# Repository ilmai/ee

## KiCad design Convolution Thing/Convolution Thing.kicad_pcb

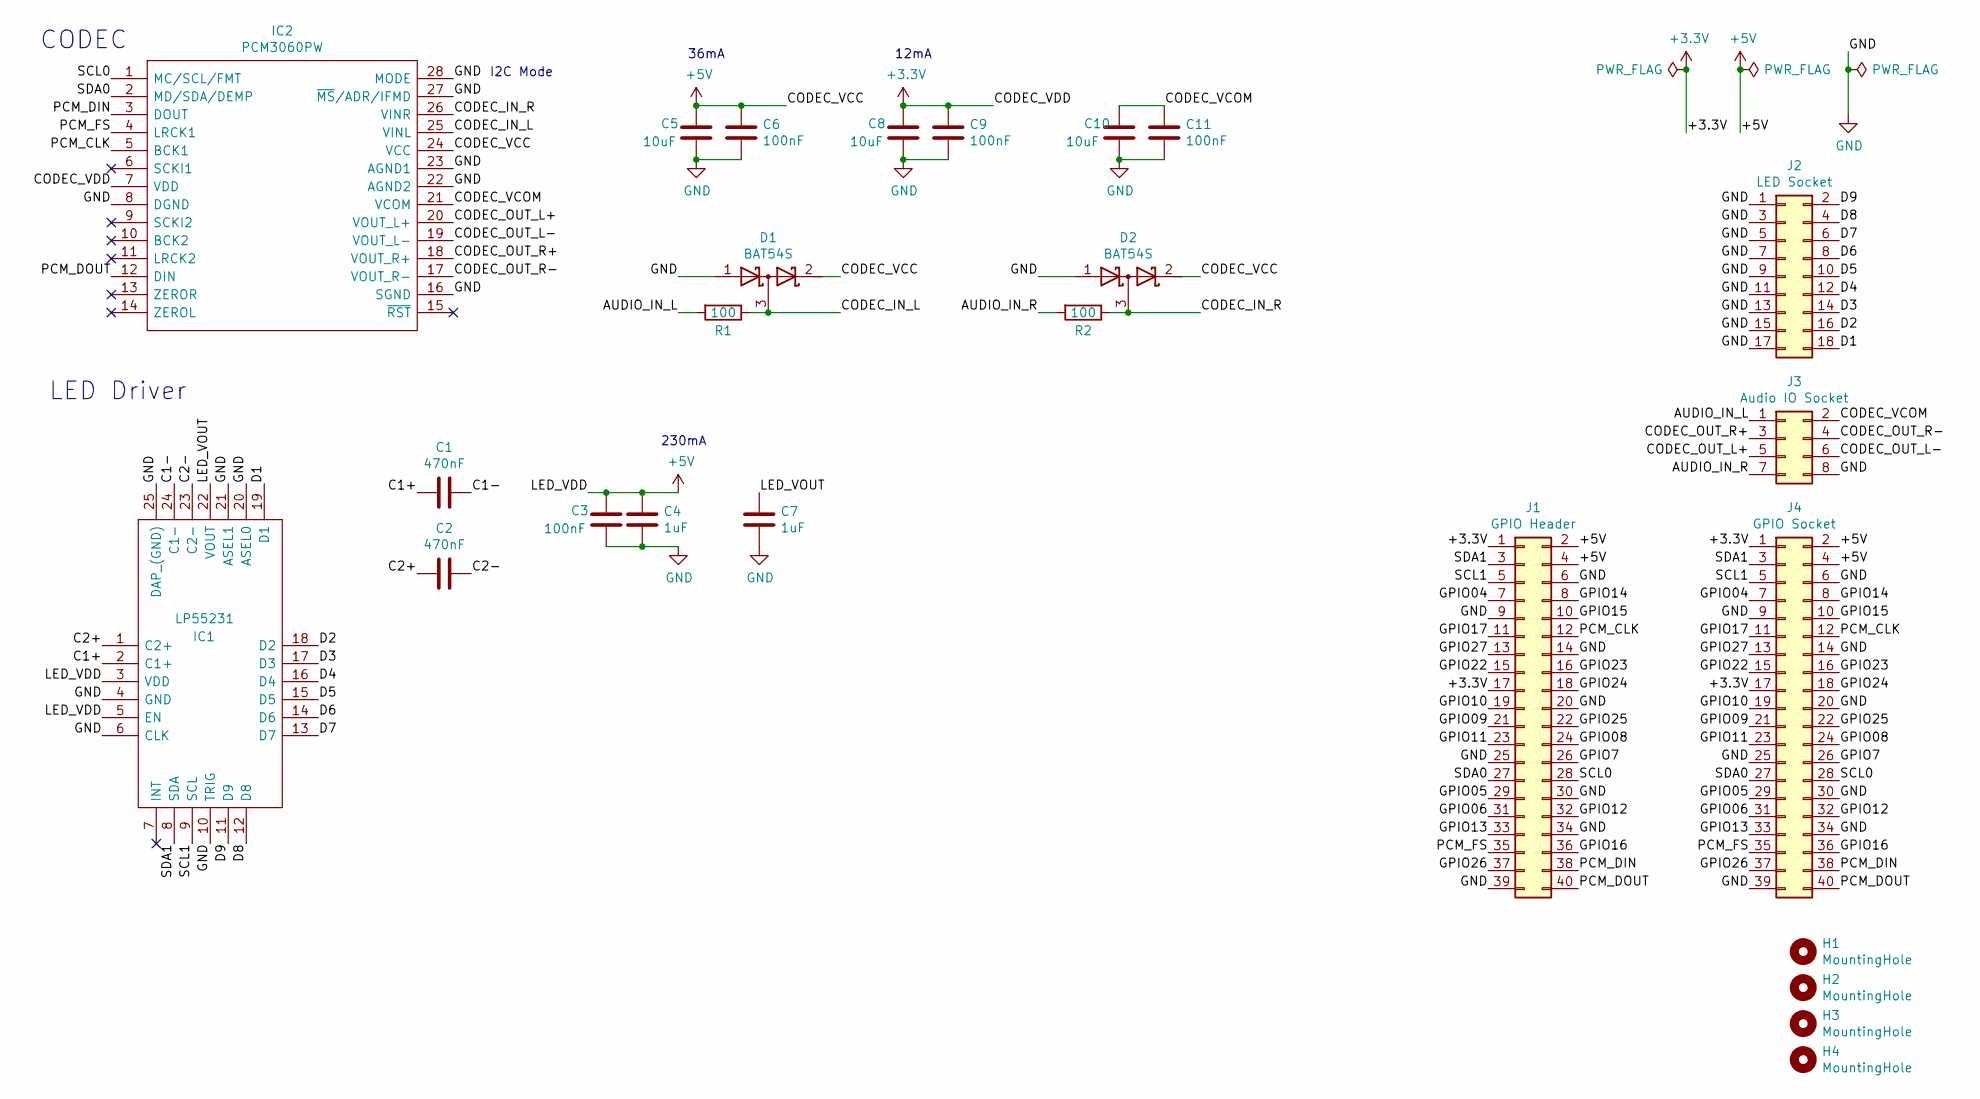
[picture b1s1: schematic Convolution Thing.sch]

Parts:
C1, C2: 470nF; C_Rect_L4.6mm_W3.0mm_P2.50mm_MKS02_FKP02
C3, C6, C9, C11: 100nF; C_Rect_L4.6mm_W3.0mm_P2.50mm_MKS02_FKP02
C4, C7: 1uF; C_Rect_L4.6mm_W3.0mm_P2.50mm_MKS02_FKP02
C5, C8, C10: 10uF; C_Rect_L4.6mm_W3.0mm_P2.50mm_MKS02_FKP02
D1, D2: BAT54S; SOT-323_SC-70_Handsoldering
H1, H2, H3, H4: MountingHole; MountingHole_2.75mm_M2.5
IC1: LP55231; QFN50P400X400X80-25N; Mouser Part Number 595-LP55231SQE/NOPB
IC2: PCM3060PW; SOP65P640X120-28N; Mouser Part Number 595-PCM3060PW
J1: GPIO Header; PinHeader_2x20_P2.54mm_Vertical
J2: LED Socket; PinSocket_2x09_P2.54mm_Vertical
J3: Audio IO Socket; PinSocket_2x04_P2.54mm_Vertical
J4: GPIO Socket; PinSocket_2x20_P2.54mm_Vertical
R1, R2: 100; R_Axial_DIN0207_L6.3mm_D2.5mm_P10.16mm_Horizontal

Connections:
+3V3: C8.1, C9.1, IC2.7 (VDD), J1.1, J1.17, J4.1, J4.17
+5V: C3.1, C4.1, C5.1, C6.1, D1.2 (K), D2.2 (K), IC1.3 (VDD), IC1.5 (EN), IC2.24 (VCC), J1.2, J1.4, J4.2, J4.4
/AUDIO_IN_L: J3.1, R1.2
/AUDIO_IN_R: J3.7, R2.2
/C1+: C1.2, IC1.2 (C1+)
/C1-: C1.1, IC1.24 (C1-)
/C2+: C2.2, IC1.1 (C2+)
/C2-: C2.1, IC1.23 (C2-)
/CODEC_IN_L: D1.3 (common), IC2.25 (VINL), R1.1
/CODEC_IN_R: D2.3 (common), IC2.26 (VINR), R2.1
/CODEC_OUT_L+: IC2.20 (VOUT_L+), J3.5
/CODEC_OUT_L-: IC2.19 (VOUT_L-), J3.6
/CODEC_OUT_R+: IC2.18 (VOUT_R+), J3.3
/CODEC_OUT_R-: IC2.17 (VOUT_R-), J3.4
/CODEC_VCOM: C10.1, C11.1, IC2.21 (VCOM), J3.2
/D1: IC1.19 (D1), J2.18
/D2: IC1.18 (D2), J2.16
/D3: IC1.17 (D3), J2.14
/D4: IC1.16 (D4), J2.12
/D5: IC1.15 (D5), J2.10
/D6: IC1.14 (D6), J2.8
/D7: IC1.13 (D7), J2.6
/D8: IC1.12 (D8), J2.4
/D9: IC1.11 (D9), J2.2
/GPIO04: J1.7, J4.7
/GPIO05: J1.29, J4.29
/GPIO06: J1.31, J4.31
/GPIO7: J1.26, J4.26
/GPIO08: J1.24, J4.24
/GPIO09: J1.21, J4.21
/GPIO10: J1.19, J4.19
/GPIO11: J1.23, J4.23
/GPIO12: J1.32, J4.32
/GPIO13: J1.33, J4.33
/GPIO14: J1.8, J4.8
/GPIO15: J1.10, J4.10
/GPIO16: J1.36, J4.36
/GPIO17: J1.11, J4.11
/GPIO22: J1.15, J4.15
/GPIO23: J1.16, J4.16
/GPIO24: J1.18, J4.18
/GPIO25: J1.22, J4.22
/GPIO26: J1.37, J4.37
/GPIO27: J1.13, J4.13
/LED_VOUT: C7.1, IC1.22 (VOUT)
/PCM_CLK: IC2.5 (BCK1), J1.12, J4.12
/PCM_DIN: IC2.3 (DOUT), J1.38, J4.38
/PCM_DOUT: IC2.12 (DIN), J1.40, J4.40
/PCM_FS: IC2.4 (LRCK1), J1.35, J4.35
/SCL0: IC2.1 (MC/SCL/FMT), J1.28, J4.28
/SCL1: IC1.9 (SCL), J1.5, J4.5
/SDA0: IC2.2 (MD/SDA/DEMP), J1.27, J4.27
/SDA1: IC1.8 (SDA), J1.3, J4.3
GND: C3.2, C4.2, C5.2, C6.2, C7.2, C8.2, C9.2, C10.2, C11.2, D1.1 (A), D2.1 (A), IC1.4 (GND), IC1.6 (CLK), IC1.10 (TRIG), IC1.20 (ASEL0), IC1.21 (ASEL1), IC1.25 (DAP_(GND)), IC2.8 (DGND), IC2.16 (SGND), IC2.22 (AGND2), IC2.23 (AGND1), IC2.27 (~MS~/ADR/IFMD), IC2.28 (MODE), J1.6, J1.9, J1.14, J1.20, J1.25, J1.30, J1.34, J1.39, J2.1, J2.3, J2.5, J2.7, J2.9, J2.11, J2.13, J2.15, J2.17, J3.8, J4.6, J4.9, J4.14, J4.20, J4.25, J4.30, J4.34, J4.39

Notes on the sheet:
I2C Mode
36mA
12mA
230mA
CODEC
LED Driver

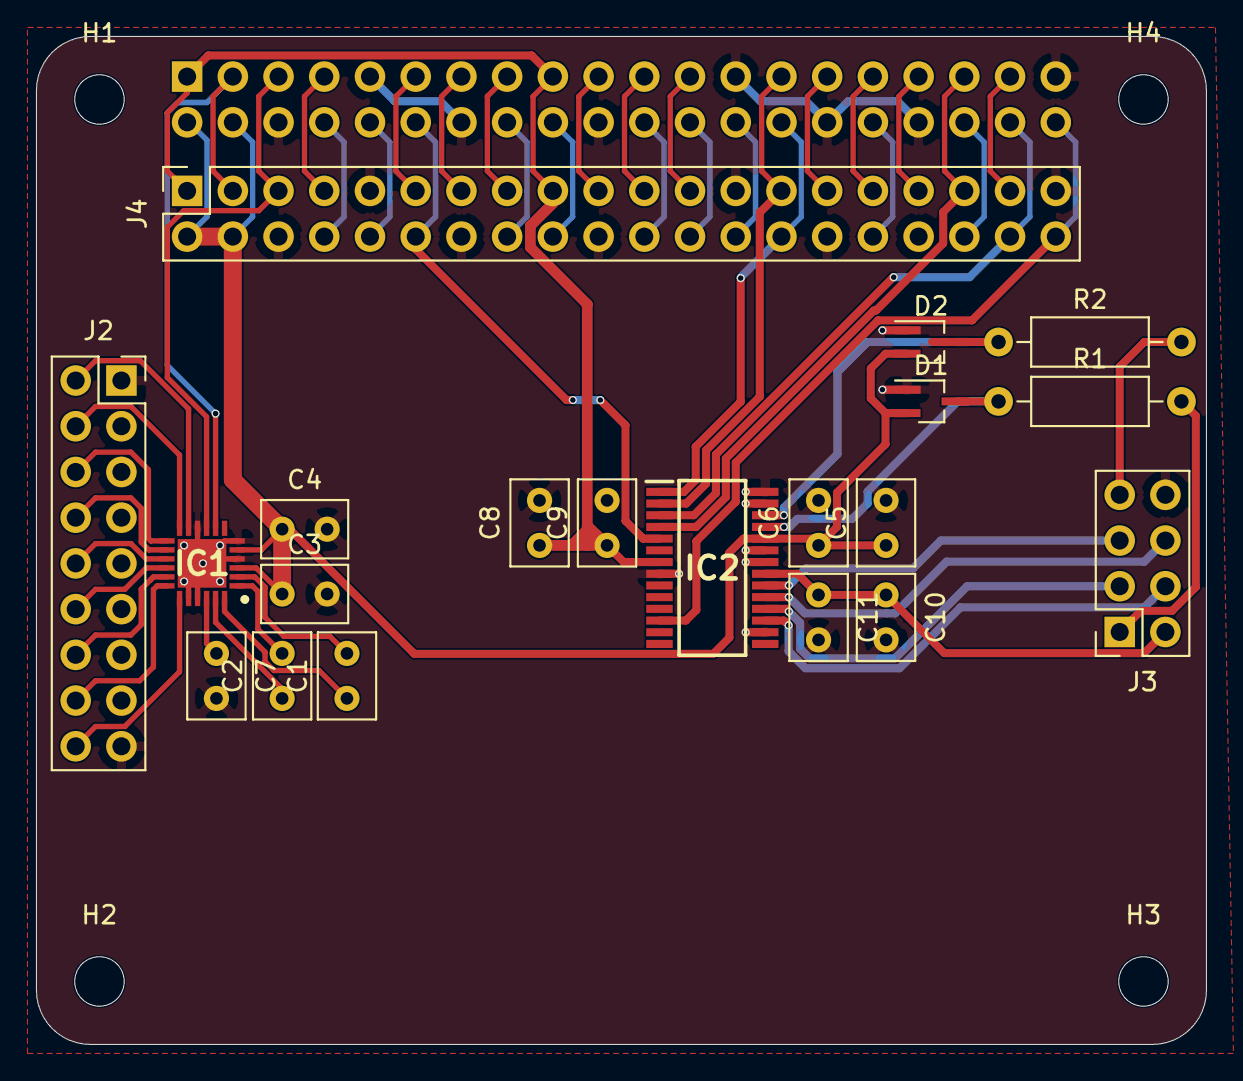
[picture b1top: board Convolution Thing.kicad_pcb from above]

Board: 2 copper layers, 65.0 x 56.0 mm, 25 parts (1 on the bottom side), 54 nets.

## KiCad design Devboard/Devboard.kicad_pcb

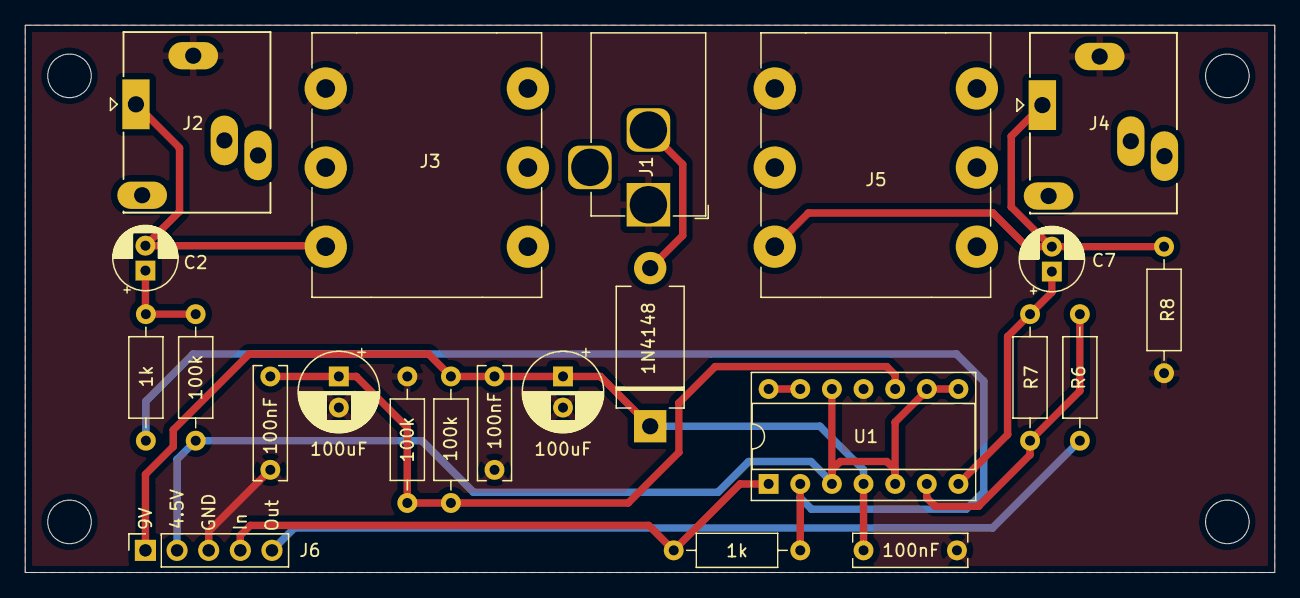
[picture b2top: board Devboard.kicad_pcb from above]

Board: 2 copper layers, 100.3 x 43.9 mm, 23 parts (0 on the bottom side), 14 nets.

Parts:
1N4148: 1N4148; D_DO-201_P12.70mm_Horizontal
1k, 1k#2: 1k; R_Axial_DIN0207_L6.3mm_D2.5mm_P10.16mm_Horizontal
100k, 100k#2, 100k#3: 100k; R_Axial_DIN0207_L6.3mm_D2.5mm_P10.16mm_Horizontal
100nF, 100nF#2, 100nF#3: 100nF; C_Rect_L9.0mm_W2.5mm_P7.50mm_MKT
100uF, 100uF#2: 100uF; CP_Radial_D6.3mm_P2.50mm
C2, C7: 10uF; CP_Radial_D5.0mm_P2.00mm
J1: 9V DC; BarrelJack_Horizontal_RoundPads
J2: In 3.5mm; Jack_3.5mm_Ledino_KB3SPRS_Horizontal
J3: In 6.3mm; Jack_6.35mm_Cliff_CL1334_Horizontal
J4: Out 3.5mm; Jack_3.5mm_Ledino_KB3SPRS_Horizontal
J5: Out 6.3mm; Jack_6.35mm_Cliff_CL1334_Horizontal
J6: I/O; PinSocket_1x05_P2.54mm_Vertical
R6, R7: 1k; R_Axial_DIN0207_L6.3mm_D2.5mm_P10.16mm_Horizontal
R8: 100k; R_Axial_DIN0207_L6.3mm_D2.5mm_P10.16mm_Horizontal
U1: TL074; DIP-14_W7.62mm_Socket

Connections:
+4.5V: 100k#3.1, J6.2, U1.3, U1.5, U1.8, U1.9, U1.12
+9V: 1N4148.1, 100k.1, 100nF.2, 100nF#3.1, 100uF#2.1, J6.1, U1.4
/Input: 1k.1, J6.4, U1.1
/Output: J6.5, R6.2
GND: 100k#2.2, 100nF.1, 100nF#2.2, 100nF#3.2, 100uF.2, 100uF#2.2, J1.1, J2.S, J3.S, J4.S, J5.S, J6.3, R8.2, U1.11
unnamed: 100k.2, 100k#2.1, 100nF#2.1, 100uF.1, U1.10
unnamed: 1k#2.2, 100k#3.2, C2.1
unnamed: C2.2, J2.T, J3.T
unnamed: C7.1, R7.1, U1.7
unnamed: C7.2, J4.T, J5.T, R8.1
unnamed: 1N4148.2, J1.2
unnamed: 1k.2, 1k#2.1, U1.2
unnamed: R6.1, R7.2, U1.6
unnamed: U1.13, U1.14

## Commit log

2021-03-20 Initial projects commit
2021-03-20 New Devboard iteration
2021-03-22 New Devboard iteration, get rid of output clipping and limit gain to unity
2021-03-22 Minor Devboard layout tweak
2021-03-24 Devboard iteration, change output filter values
2021-07-27 Devboard iteration
2021-07-27 Convolution Thing PCB, first commit
2021-07-30 Just EE things
2021-07-31 Convolution Thing PCB design continues
2021-08-01 Work on CODEC and In/Out stages
2021-08-03 New stereo codec and related changes. RIP multi-channel audio.
2021-08-03 Audio I/O, CV input, GPIO work & misc changes
2021-08-04 Better CV inputs, LED driver, display & USB interfaces
2021-08-05 Added gate inputs and CM4 / display sockets, made CV inputs 100k, lots of smaller changes. First iteration of schematic now done.
2021-08-05 Fix some issues, add component references
2021-08-05 Started footprint assignment
2021-08-06 Assign all footprints
2021-08-07 PCB layout work and related changes to the schematic
2021-08-08 PCB layout
2021-08-09 Entirely new, simpler PCB
